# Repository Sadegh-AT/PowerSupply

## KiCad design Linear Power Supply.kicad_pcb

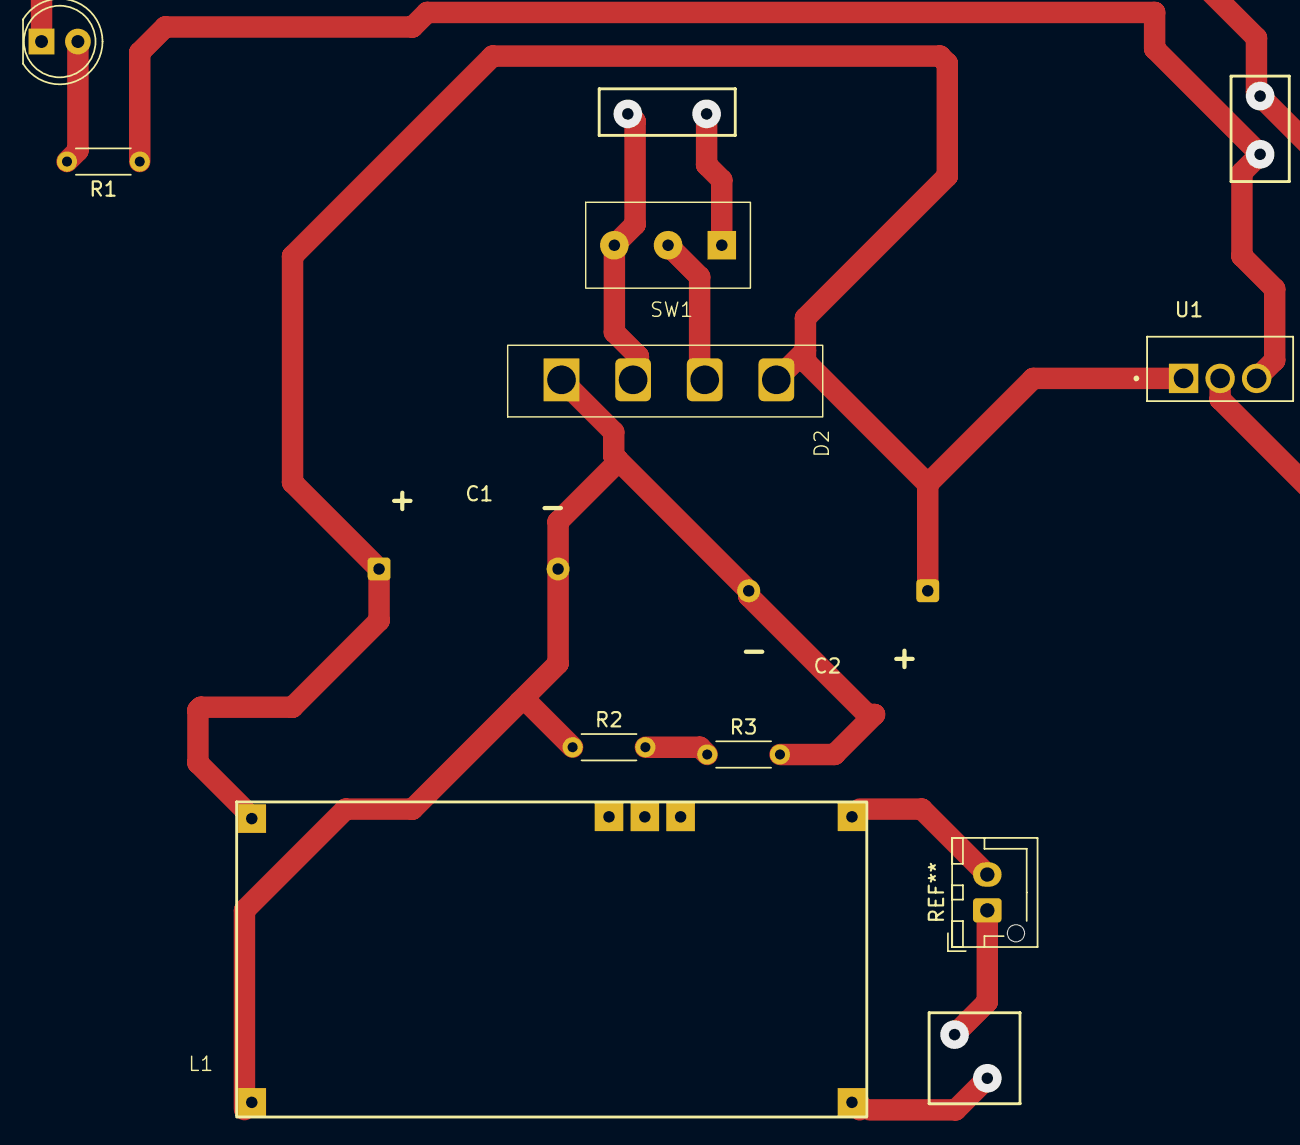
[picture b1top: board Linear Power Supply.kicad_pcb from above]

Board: 2 copper layers, 10 parts (0 on the bottom side), 5 nets.

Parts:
C1: 50v-4600µF; Cap-50v-4600
C2: 50V-4600µF; Cap-50v-4600
D1: LED; LED_D5.0mm
D2: GBU8005; diod
L1: LM2596 Moudule; lm2596
R1: 100; R_Axial_DIN0204_L3.6mm_D1.6mm_P5.08mm_Horizontal
R2, R3: 2K; R_Axial_DIN0204_L3.6mm_D1.6mm_P5.08mm_Horizontal
SW1: SW_Nidec_CAS-120A1; Switch SPST
U1: L7805; TO255P1020X450X2000-3

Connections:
GND: C1.2, C2.2, D1.1 (K), D2.1 (GND), L1.2 (IN-), R2.1, R2.2, R3.1, R3.2, U1.2 (GND)
unnamed: D1.2 (A), R1.2
unnamed: C1.1, C2.1, D2.4 (VCC), L1.1 (IN+), U1.1 (IN)
unnamed: D2.2 (AC), SW1.2 (B)
unnamed: R1.1, U1.3 (OUT)

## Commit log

2025-10-22 first
2025-10-22 test
2025-10-31 fix issue
